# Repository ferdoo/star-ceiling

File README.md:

# star ceiling
This is home project Star ceiling driver for ATmega328 ( used Nano ATmega328 Board https://ebay.us/LkKyWj )
Driver is without mechanical parts.

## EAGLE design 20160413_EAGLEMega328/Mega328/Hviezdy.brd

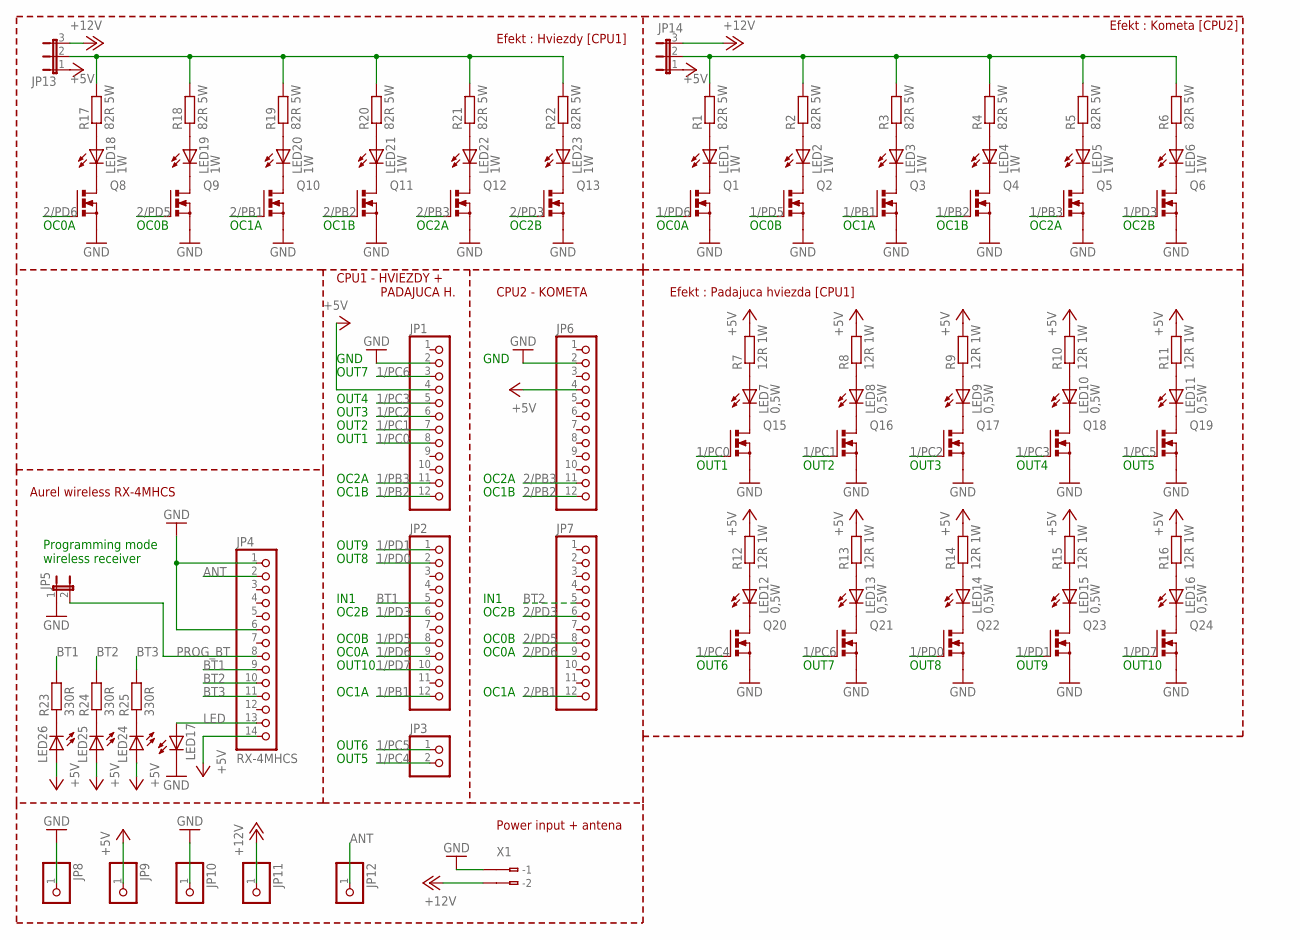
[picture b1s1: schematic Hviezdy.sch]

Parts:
JP1, JP2, JP6, JP7: PINHD-1X12; 1X12
JP3: PINHD-1X2; 1X02
JP4: RX-4MHCS; 1X14
JP5: JP1E; JP1
JP8, JP9, JP10, JP11, JP12: PINHD-1X1; 1X01
JP13, JP14: JP2E; JP2
LED1, LED2, LED3, LED4, LED5, LED6, LED18, LED19, LED20, LED21, LED22, LED23: 1W; LED5MM
LED7, LED8, LED9, LED10, LED11, LED12, LED13, LED14, LED15, LED16: 0,5W; LED10MM
LED17, LED24, LED25, LED26: LED3MM
Q1, Q2, Q3, Q4, Q5, Q6, Q8, Q9, Q10, Q11, Q12, Q13, Q15, Q16, Q17, Q18, Q19, Q20, Q21, Q22, Q23, Q24: PMOSFET_NTO220BV; TO220BV
R1, R2, R3, R4, R5, R6, R17, R18, R19, R20, R21, R22: 82R 5W; 0922V
R7, R8, R9, R10, R11, R12, R13, R14, R15, R16: 12R 1W; 0309/12
R23, R24, R25: 330R; 0207/12
X1: 234-202

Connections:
1/PB1: JP2.12, Q3.G
1/PB2: JP1.12, Q4.G
1/PB3: JP1.11, Q5.G
1/PC0: JP1.8, Q15.G
1/PC1: JP1.7, Q16.G
1/PC2: JP1.6, Q17.G
1/PC3: JP1.5, Q18.G
1/PC4: JP3.2, Q20.G
1/PC5: JP3.1, Q19.G
1/PC6: JP1.3, Q21.G
1/PD0: JP2.2, Q22.G
1/PD1: JP2.1, Q23.G
1/PD3: JP2.6, Q6.G
1/PD5: JP2.8, Q2.G
1/PD6: JP2.9, Q1.G
1/PD7: JP2.10, Q24.G
2/PB1: JP7.12, Q10.G
2/PB2: JP6.12, Q11.G
2/PB3: JP6.11, Q12.G
2/PD3: JP7.6, Q13.G
2/PD5: JP7.8, Q9.G
2/PD6: JP7.9, Q8.G
+5V: JP1.4, JP4.14, JP6.4, JP9.1, JP13.1, JP14.1, LED24.A, LED25.A, LED26.A, R7.2, R8.2, R9.2, R10.2, R11.2, R12.2, R13.2, R14.2, R15.2, R16.2
+12V: JP11.1, JP13.3, JP14.3, X1.B2 (B-2)
ANT: JP4.2, JP12.1
BT1: JP2.5, JP4.9, R23.2
BT2: JP4.10, JP7.5, R24.2
BT3: JP4.11, R25.2
GND: JP1.2, JP4.1, JP4.6, JP5.1, JP6.2, JP8.1, JP10.1, LED17.K (C), Q1.S, Q2.S, Q3.S, Q4.S, Q5.S, Q6.S, Q8.S, Q9.S, Q10.S, Q11.S, Q12.S, Q13.S, Q15.S, Q16.S, Q17.S, Q18.S, Q19.S, Q20.S, Q21.S, Q22.S, Q23.S, Q24.S, X1.B1 (B-1)
LED: JP4.13, LED17.A
unnamed: LED1.K (C), Q1.D
unnamed: LED2.K (C), Q2.D
unnamed: LED3.K (C), Q3.D
unnamed: LED4.K (C), Q4.D
unnamed: LED5.K (C), Q5.D
unnamed: LED6.K (C), Q6.D
unnamed: LED1.A, R1.1
unnamed: LED2.A, R2.1
unnamed: LED3.A, R3.1
unnamed: LED4.A, R4.1
unnamed: LED5.A, R5.1
unnamed: LED6.A, R6.1
unnamed: LED7.A, R7.1
unnamed: LED7.K (C), Q15.D
unnamed: LED8.K (C), Q16.D
unnamed: LED9.K (C), Q17.D
unnamed: LED10.K (C), Q18.D
unnamed: LED11.K (C), Q19.D
unnamed: LED12.K (C), Q20.D
unnamed: LED8.A, R8.1
unnamed: LED9.A, R9.1
unnamed: LED10.A, R10.1
unnamed: LED11.A, R11.1
unnamed: LED12.A, R12.1
unnamed: LED13.A, R13.1
unnamed: LED14.A, R14.1
unnamed: LED13.K (C), Q21.D
unnamed: LED15.A, R15.1
unnamed: LED14.K (C), Q22.D
unnamed: LED16.A, R16.1
unnamed: LED15.K (C), Q23.D
unnamed: LED18.K (C), Q8.D
unnamed: LED16.K (C), Q24.D
unnamed: LED19.K (C), Q9.D
unnamed: LED20.K (C), Q10.D
unnamed: LED21.K (C), Q11.D
unnamed: LED22.K (C), Q12.D
unnamed: LED23.K (C), Q13.D
unnamed: LED18.A, R17.1
unnamed: LED19.A, R18.1
unnamed: LED20.A, R19.1
unnamed: LED21.A, R20.1
unnamed: LED22.A, R21.1
unnamed: LED23.A, R22.1
unnamed: LED26.K (C), R23.1
unnamed: LED25.K (C), R24.1
unnamed: LED24.K (C), R25.1
unnamed: JP13.2, R17.2, R18.2, R19.2, R20.2, R21.2, R22.2
unnamed: JP14.2, R1.2, R2.2, R3.2, R4.2, R5.2, R6.2
PROG_BT: JP4.8, JP5.2

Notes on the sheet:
OC0A
OC0B
OC1A
OC1B
OC2A
OC2B
OUT1
OUT2
OUT3
OUT4
OUT5
OUT6
OUT7
OUT8
OUT9
OUT10
GND
Programming mode wireless receiver
Efekt : Kometa [CPU2]
Efekt : Padajuca hviezda [CPU1]
CPU1 - HVIEZDY + PADAJUCA H.
CPU2 - KOMETA
Aurel wireless RX-4MHCS
Efekt : Hviezdy [CPU1]
IN1
Power input + antena

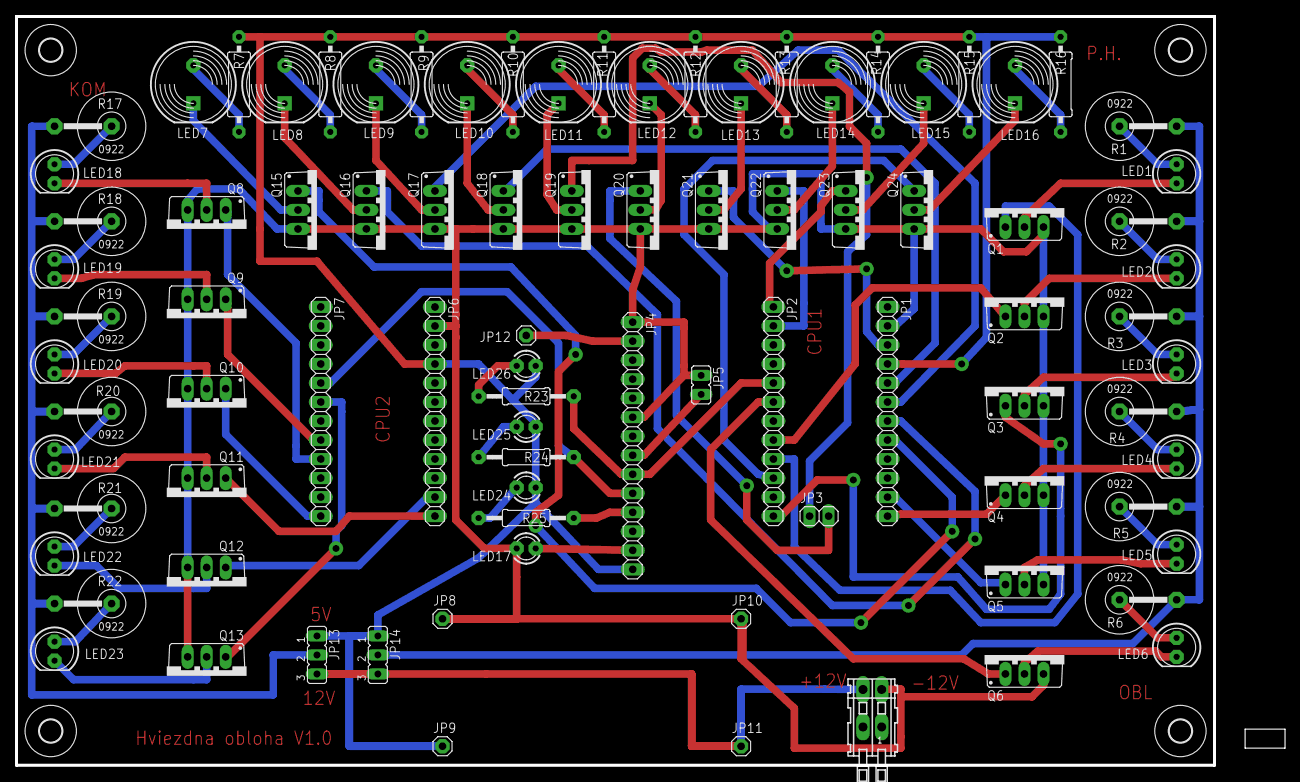
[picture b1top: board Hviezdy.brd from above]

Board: 2 copper layers, 169.2 x 100.0 mm, 92 parts (0 on the bottom side), 80 nets.

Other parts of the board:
U$1, U$2, U$3, U$4: 3,0

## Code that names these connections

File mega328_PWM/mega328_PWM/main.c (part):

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Timer/Counter1 has 2 outputs, OC1A and OC1B
Timer/Counter2 has 2 outputs, OC2A and OC2B

PIN1	PD3	OC2B (Timer/Counter2)
PIN9	PD5	OC0B (Timer/Counter0)
PIN10	PD6	OC0A (Timer/Counter0)

PIN13	PB1	OC1A (Timer/Counter1)
PIN14	PB2	OC1B (Timer/Counter1)
PIN15	PB3	OC2A (Timer/Counter2)

TCCR0A	Timer/Counter Control Register 0 A
WGM		Waveform Generator Mode bits
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11. zmena PWM na phase correct (pri fast PWM a zapise do OCRxx = 0 LED trochu svieti)
12. pridanie prerusenie pre timer1 - nastane pri preteceni casovaca, pouzije sa na oddialenie inkrementacie daneho PWM cim sa spomali
    docieli sa rozna rychlosn na vsetkych PWM kanaloch
13. pridal sa vstup INT0 - prerusenie na prepinanie efektov a zmena posledneho bitu pri padajucej hviezde z PD2 na PD7 kedze PD2 sa zacalo pouzivat ako vstup
14. pridanie vystupov padajucej hviezdy pod program prerusenia / oprava sw pri OCR = 255 led nesvietili ale preblikavali
15. pridanie pola s casom na aktualizaciu padajucej hviezdy
*******************************************************************/ 
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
